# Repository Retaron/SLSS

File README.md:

# SLSS
Code for hobby project of mushroom manager

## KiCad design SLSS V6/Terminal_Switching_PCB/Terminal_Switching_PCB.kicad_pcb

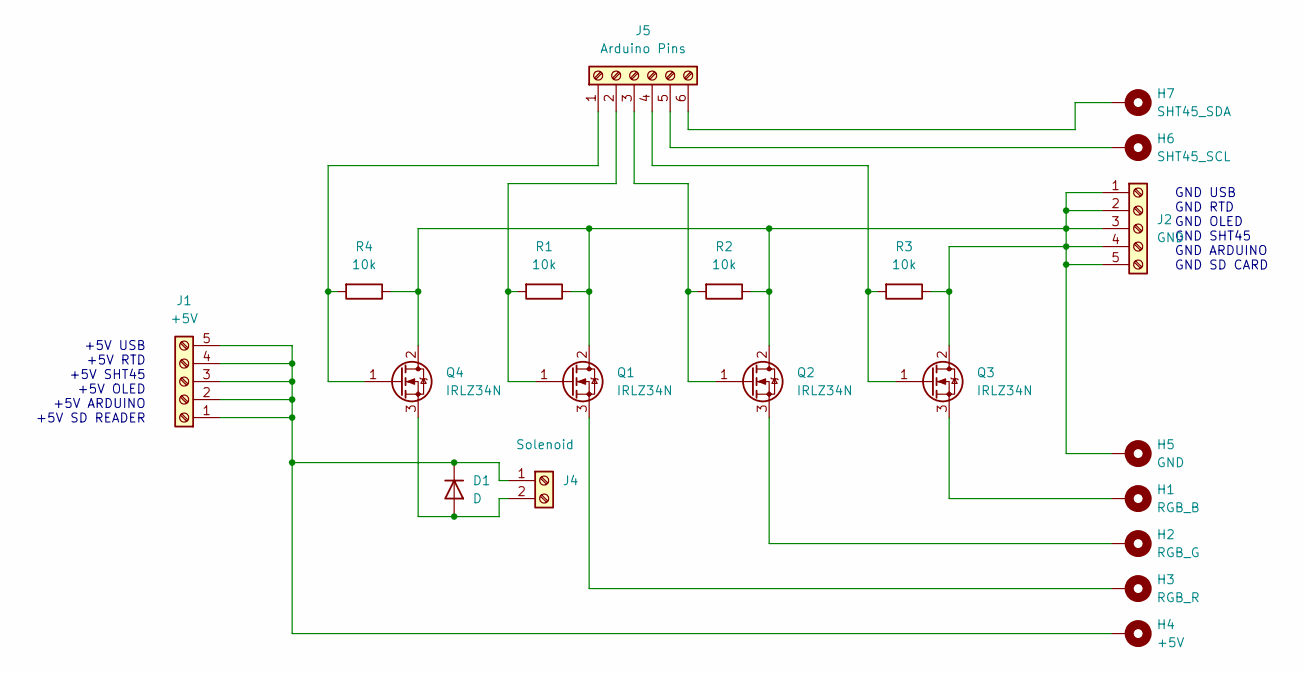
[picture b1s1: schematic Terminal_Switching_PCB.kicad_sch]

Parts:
D1: D; D_A-405_P10.16mm_Horizontal
H1: RGB_B; MountingHole_3.2mm_M3_Pad_Via
H2: RGB_G; MountingHole_3.2mm_M3_Pad_Via
H3: RGB_R; MountingHole_3.2mm_M3_Pad_Via
H4: +5V; MountingHole_3.2mm_M3_Pad_Via
H5: GND; MountingHole_3.2mm_M3_Pad_Via
H6: SHT45_SCL; MountingHole_3.2mm_M3_Pad_Via
H7: SHT45_SDA; MountingHole_3.2mm_M3_Pad_Via
J1: +5V; TerminalBlock_Phoenix_MPT-0,5-5-2.54_1x05_P2.54mm_Horizontal
J2: GND; TerminalBlock_Phoenix_MPT-0,5-5-2.54_1x05_P2.54mm_Horizontal
J4: Solenoid; JST_XH_B2B-XH-A_1x02_P2.50mm_Vertical
J5: Arduino Pins; TerminalBlock_Phoenix_MPT-0,5-6-2.54_1x06_P2.54mm_Horizontal
Q1, Q2, Q3, Q4: IRLZ34N; TO-220-3_Vertical
R1, R2, R3, R4: 10k; R_Axial_DIN0207_L6.3mm_D2.5mm_P10.16mm_Horizontal

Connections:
unnamed: D1.2 (A), J4.2, Q4.3 (S)
unnamed: D1.1 (K), H4.1 (1_1), J1.1, J1.2, J1.3, J1.4, J1.5, J4.1
unnamed: H5.1 (1_1), J2.1, J2.2, J2.3, J2.4, J2.5, Q1.2 (D), Q2.2 (D), Q3.2 (D), Q4.2 (D), R1.1, R2.1, R3.1, R4.1
unnamed: J5.1, Q4.1 (G), R4.2
unnamed: J5.2, Q1.1 (G), R1.2
unnamed: J5.3, Q2.1 (G), R2.2
unnamed: J5.4, Q3.1 (G), R3.2
unnamed: H6.1 (1_1), J5.5
unnamed: H7.1 (1_1), J5.6
unnamed: H3.1 (1_1), Q1.3 (S)
unnamed: H2.1 (1_1), Q2.3 (S)
unnamed: H1.1 (1_1), Q3.3 (S)

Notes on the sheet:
+5V USB +5V RTD +5V SHT45 +5V OLED +5V ARDUINO +5V SD READER
GND USB GND RTD GND OLED GND SHT45 GND ARDUINO GND SD CARD

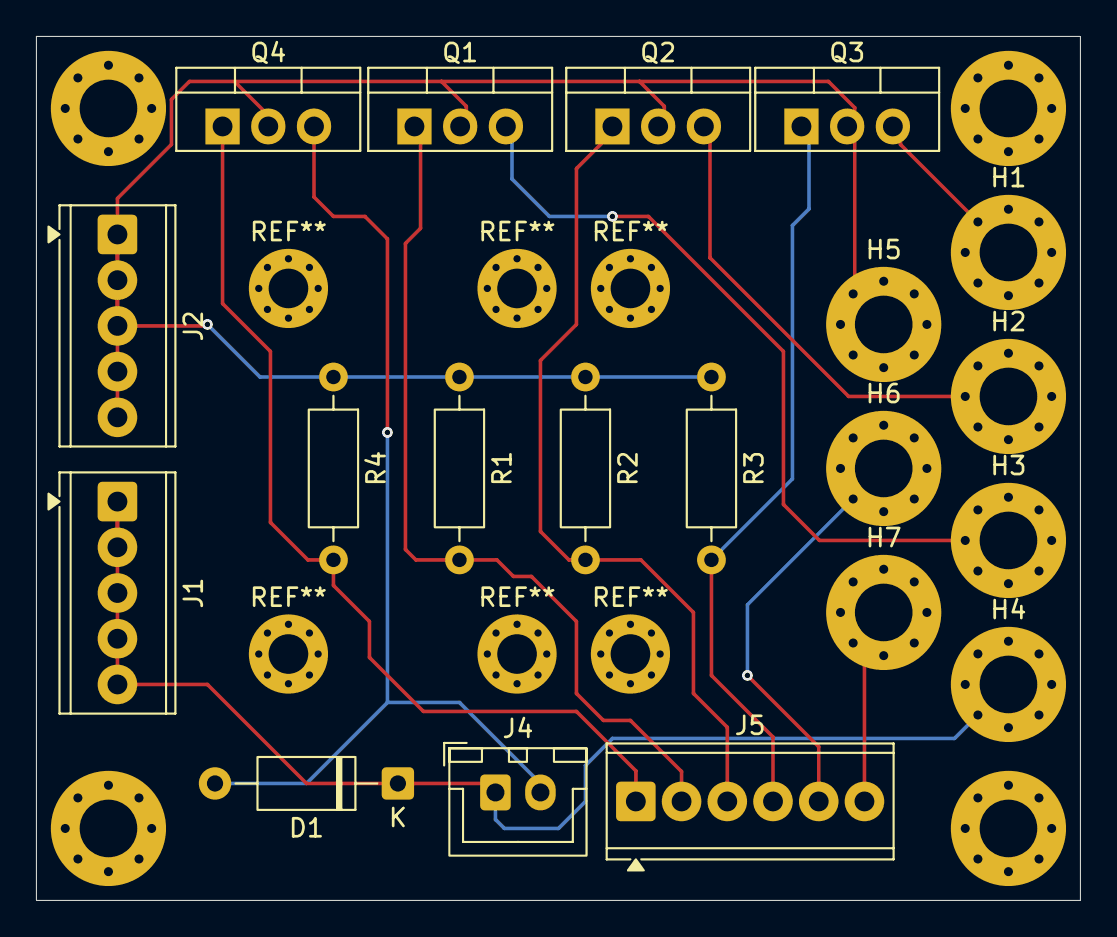
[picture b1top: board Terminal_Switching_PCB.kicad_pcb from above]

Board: 2 copper layers, 58.0 x 48.0 mm, 20 parts (0 on the bottom side), 12 nets.

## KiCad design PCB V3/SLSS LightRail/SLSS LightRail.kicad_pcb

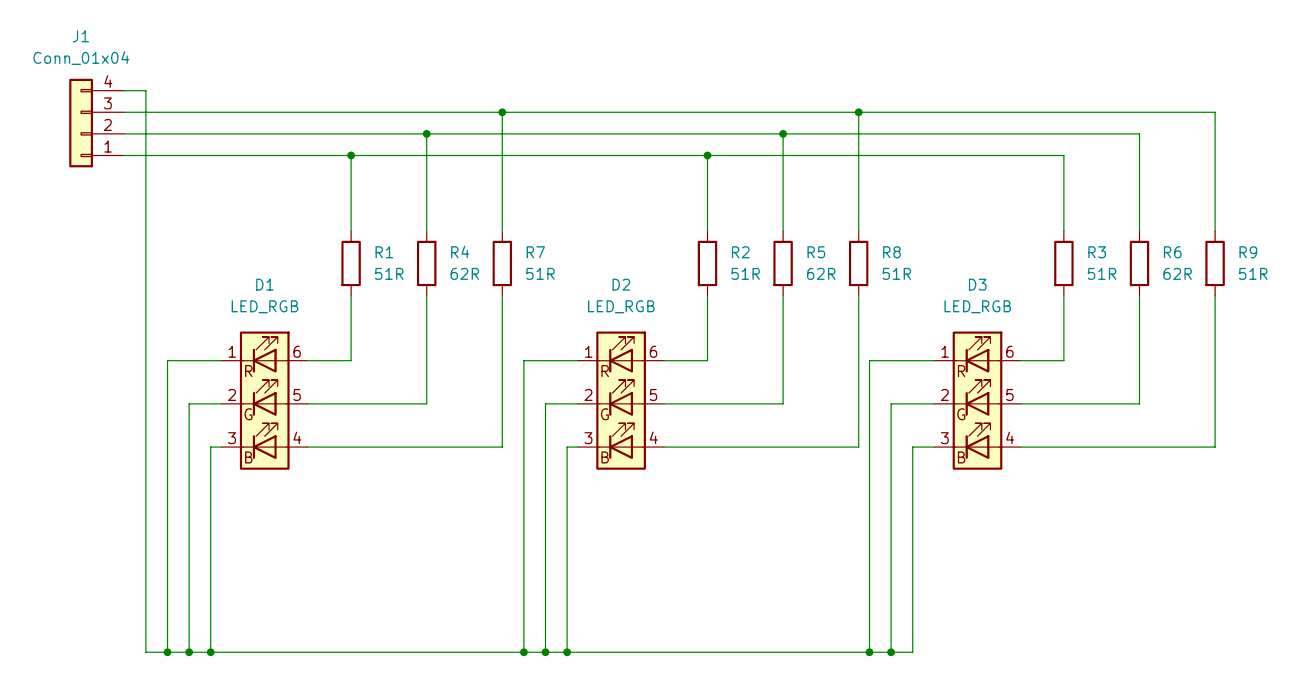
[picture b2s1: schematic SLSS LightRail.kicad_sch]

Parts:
D1, D2, D3: LED_RGB; LED_RGB_5050-6
J1: Conn_01x04; JST_GH_SM04B-GHS-TB_1x04-1MP_P1.25mm_Horizontal
R1, R2, R3, R7, R8, R9: 51R; R_1206_3216Metric
R4, R5, R6: 62R; R_1206_3216Metric

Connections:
unnamed: D1.4 (BA), R7.2
unnamed: D1.1 (RK), D1.2 (GK), D1.3 (BK), D2.1 (RK), D2.2 (GK), D2.3 (BK), D3.1 (RK), D3.2 (GK), D3.3 (BK), J1.4
unnamed: D1.5 (GA), R4.1
unnamed: D1.6 (RA), R1.2
unnamed: D2.4 (BA), R8.2
unnamed: D2.5 (GA), R5.2
unnamed: D2.6 (RA), R2.2
unnamed: D3.4 (BA), R9.2
unnamed: D3.5 (GA), R6.2
unnamed: D3.6 (RA), R3.2
unnamed: J1.1, R1.1, R2.1, R3.1
unnamed: J1.2, R4.2, R5.1, R6.1
unnamed: J1.3, R7.1, R8.1, R9.1

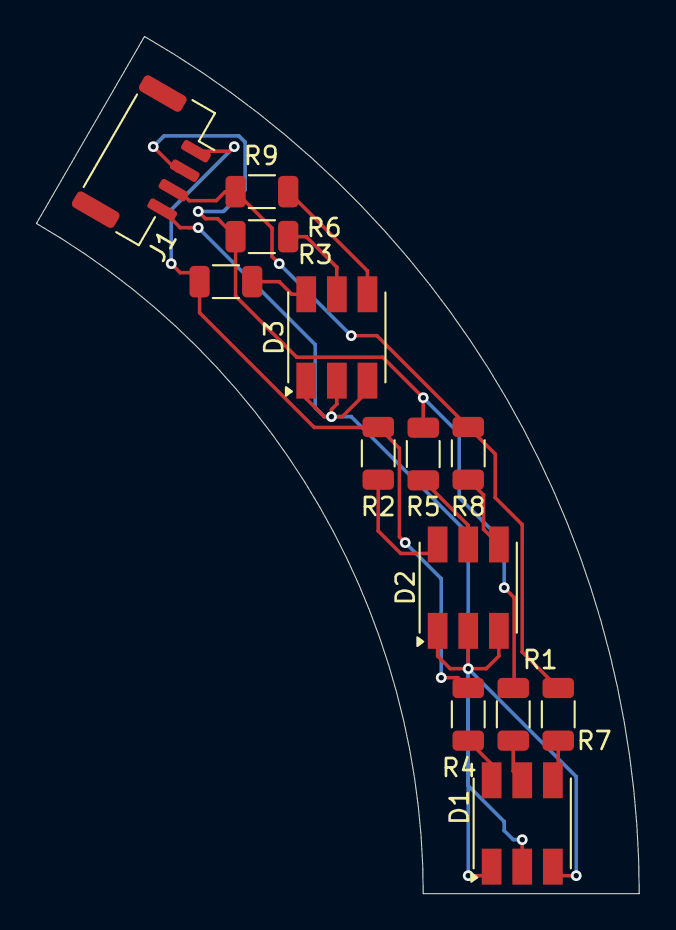
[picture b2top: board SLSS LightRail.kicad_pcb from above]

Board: 2 copper layers, 33.5 x 47.6 mm, 13 parts (0 on the bottom side), 13 nets.

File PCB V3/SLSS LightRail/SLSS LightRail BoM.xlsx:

Reference | Qty | Value | DNP | Exclude from BOM | Exclude from Board | Footprint | Datasheet | Manufacturer part number | Supplier part number | Supplier | Manufacturer
D1,D2,D3 | 3 | LED_RGB |  |  |  | LED_SMD:LED_RGB_5050-6 | KAAF-5050RGBS-13 LED Data Sheet | KAAF-5050RGBS-13 | 872-1724 | RS components | Kingbright
J1 | 1 | Conn_01x04 |  |  |  | Connector_JST:JST_XA_S04B-XASK-1_1x04_P2.50mm_Horizontal | Datasheet | S04B-XASK-1 (LF)(SN) | 602-8228 | RS components | JST
R1,R2,R3,R7,R8,R9 | 6 | 51R |  |  |  | Resistor_SMD:R_1206_3216Metric | Document - SR2512MK-071R3L | SR1206JR-0751RL | 197-8432 | RS components | Yageo
R4,R5,R6 | 3 | 62R |  |  |  | Resistor_SMD:R_1206_3216Metric | Datasheet - RC |  | 198-8437 | RS components | Yageo

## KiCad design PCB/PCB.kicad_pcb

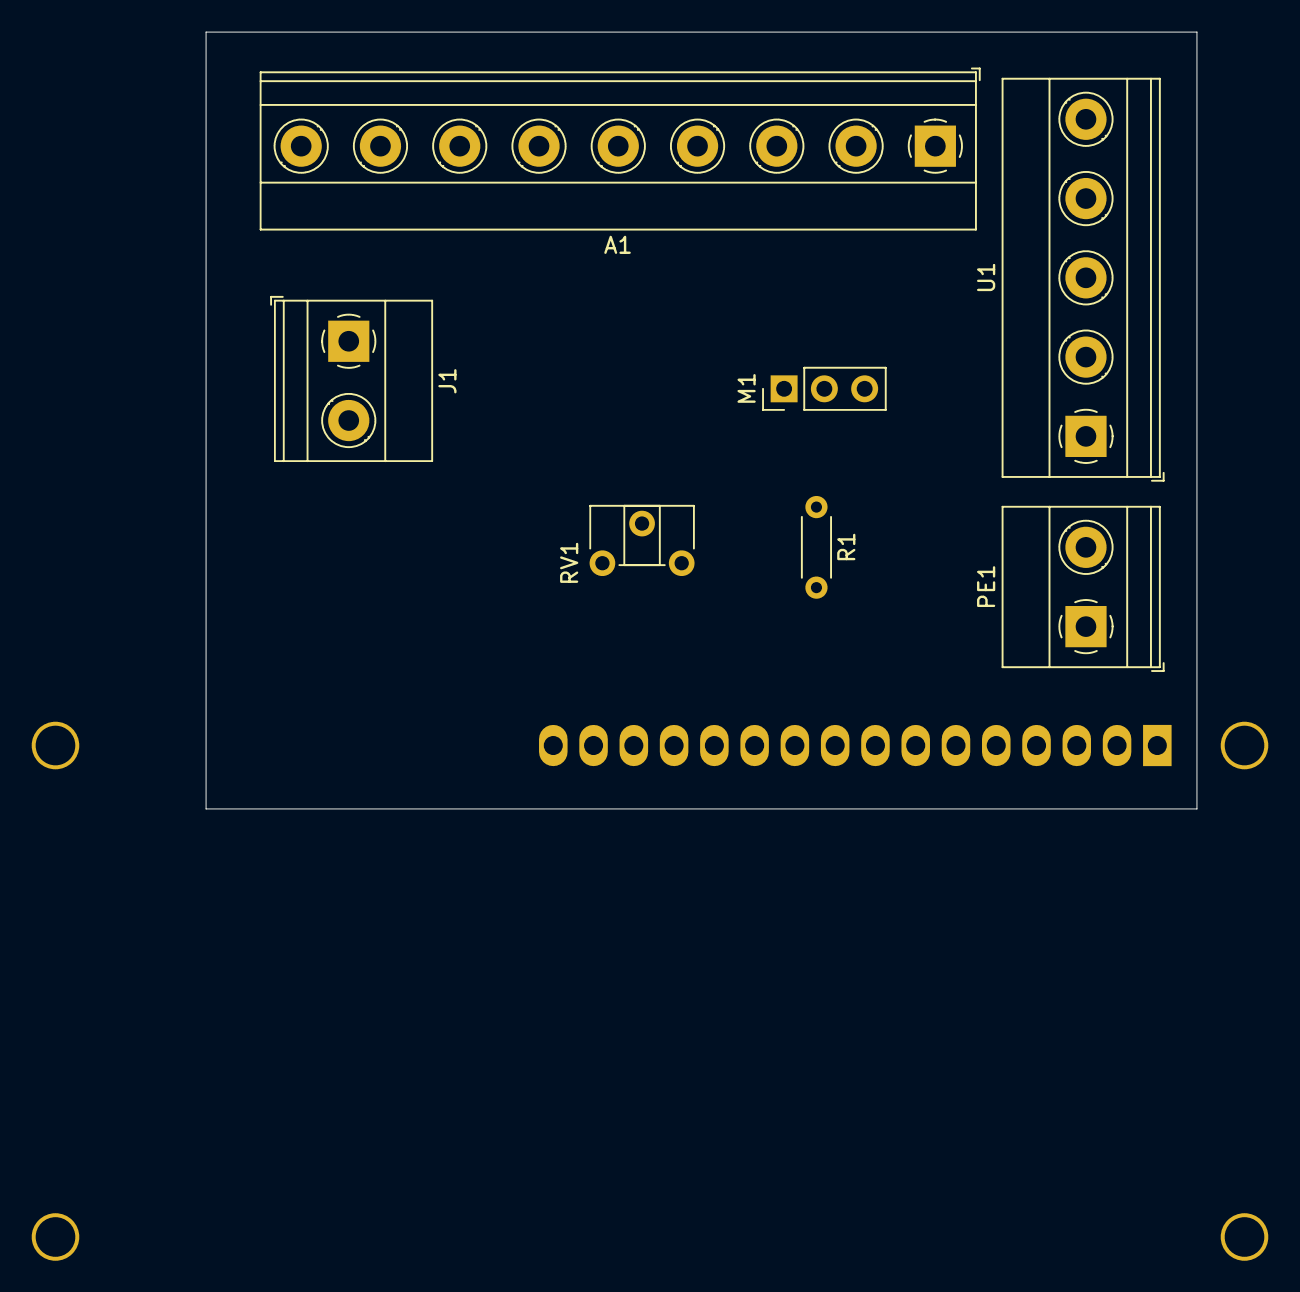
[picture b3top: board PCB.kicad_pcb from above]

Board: 2 copper layers, 62.5 x 49.0 mm, 8 parts (1 on the bottom side), 7 nets, no tracks yet.

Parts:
A1: Arduino_UNO_R3; TerminalBlock_Phoenix_MKDS-1,5-9_1x09_P5.00mm_Horizontal
DS1: WC1602A
J1: Barrel_Jack; TerminalBlock_Phoenix_MKDS-1,5-2_1x02_P5.00mm_Horizontal
M1: Motor_Servo; PinHeader_1x03_P2.54mm_Vertical
PE1: PeltierElement; TerminalBlock_Phoenix_MKDS-1,5-2_1x02_P5.00mm_Horizontal
R1: 220; R_Axial_DIN0204_L3.6mm_D1.6mm_P5.08mm_Horizontal
RV1: R_Potentiometer; Potentiometer_ACP_CA6-H2,5_Horizontal
U1: L298N; TerminalBlock_Phoenix_MKDS-1,5-5_1x05_P5.00mm_Horizontal

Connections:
unnamed: A1.5 (+5V), DS1.2 (VDD), R1.2, RV1.3
unnamed: DS1.15 (LED(+)), R1.1
unnamed: A1.7 (GND), DS1.1 (VSS), DS1.5 (R/W), DS1.16 (LED(-)), J1.2, RV1.1
unnamed: DS1.3 (VO), RV1.2
unnamed: PE1.1, U1.2 (OUT1)
unnamed: PE1.2, U1.3 (OUT2)
unnamed: J1.1, U1.4 (Vs)

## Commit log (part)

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2025-09-22 Created SLSS.ino
    Uploaded previously worked on SLSS.ino as a template and added function relating to reading from the current sensor
2025-09-22 minor changes
2025-09-23 Updated pins
    moved LCD pins to digital since they dont need PWM
2025-09-23 Rotary encoder & LCD Pages
    reorganised pins again due to rotary encoder only working on pins 2 & 3. added pages to LCD with rotary encoder.
    TODO: added click to modify values and possibly fix encoder direction accuraccy
2025-09-24 Fixed rotary encoder Inaccuracy
    fixed inaccuracy by stealing some strange serial code from somewhere else
2025-09-24 Better format + fixes
    adding a small delay fixes the occasional miss by the rotary encoder. Reformatted code for page interaction.
2025-09-24 began RGB edit
2025-09-25 Prototype RBG edit
    Added select for RGB values
2025-09-25 more rgb updates
2025-10-22 RGB edit implemented
    Fully implemented RGB page, including displaying the values and editing them using the rotary encoder
2025-10-22 Added RGB led pinout
    Added function and set the pins for the RGB LED
2025-10-23 broke it lol
2025-10-27 fixed page issue
    for whatever reason, when defining variables inside a function, the page wont change
2025-10-27 added switch
2025-10-28 krap
2025-10-29 DHT testing
    simple DHT11 sensor test, pretty sure the one I am using is broken
2025-10-29 Fixed DHT11
    fixed DHT11 by using a different library, the library recommends a polling rate of 1Hz however it seems to update instantly on the LCD when using the normal loops delay of 50ms
2025-10-30 Moved repo
2025-11-03 Update entire repo
2025-11-04 3D printng
2025-11-04 added external models
2025-11-06 3D prints
2025-11-10 Printing PSU box fast
    printing PSU box with fast parameters (0.6n 40mm layer height)
2025-11-15 Step files for collaboration
2025-11-18 external file
2025-11-18 V3
    YEsss James all is good
2025-11-18 Updated BOM
2025-11-19 new BoM for v3
2025-11-20 Did some more work
2025-11-21 Added bottle chassis prototype
2025-11-21 Yeess Some more work
2025-11-21 added part to bom
2025-11-21 iygv
2025-11-21 Started PCB
2025-11-22 testing github
2025-11-22 Started the 4 Verson
2025-11-23 Some Even More Work
2025-11-23 ouvy
2025-11-23 Updated KiCad Schematic
    Included arduino nano trace and USB-C connector
2025-11-24 Yeess
2025-11-24 yesss
2025-11-24 Added hatching to cover
2025-11-24 Added LCD and file management
2025-11-24 More Work
2025-11-25 Yresss
2025-11-25 Added filter patch hole
2025-11-25 spine
2025-11-25 YESA
2025-11-25 Yrwesa
2025-11-26 yeeesss
2025-11-26 Printed knob
2025-11-26 Minor changes
    renamed assembly, created air tunnel assembly
2025-11-27 Air tunnel rework
2025-11-27 PCB Backup
2025-11-27 Screen documentation
2025-11-27 Fan tunnel design
2025-11-27 Air Tunnel modifications
2025-11-28 V5 BOTTLE AND REQUIREMENTS
2025-11-29 TYCGHV
2025-11-29 Bottle servo push test
2025-11-30 Research of UV light
2025-11-30 LED mount
2025-12-01 Added SMD LED to BoM
2025-12-01 printing test rigs
2025-12-01 LED rail
2025-12-02 Began LED PCB
2025-12-02 Minor alterations to LED PCB
2025-12-02 horn gears
2025-12-03 light rail PCB
2025-12-03 Finished Lightrail PCB
2025-12-03 PCB size fix
2025-12-03 Mirror PCB
2025-12-03 Began bottle push mechanism
2025-12-04 Rack and pinion for servo
2025-12-04 3D Print gear
2025-12-06 drawer
2025-12-07 bottledrw
2025-12-07 shgfrga
2025-12-08 Rail partition
2025-12-10 bottle rail edit
2025-12-10 external latch model
2025-12-12 nothing
2025-12-22 drawer lokcing mechanism
2025-12-24 Lock mechanism
2025-12-27 printer files
2025-12-30 servo interface files
2026-01-02 servo interface
2026-01-03 Bottle Servo gear
2026-01-04 Gear draw
2026-01-05 print files
2026-01-05 test rig for draw
2026-01-18 air tunnel rework
    reworked air tunnel so it can be sealed
2026-01-19 3D Print files
2026-01-20 heat sink fit
2026-03-02 Gear test rework
2026-03-06 3d print file
2026-03-10 Ordered PCB
2026-03-12 rework clamp design
2026-03-12 bleh
2026-03-12 backup ig
2026-06-06 Created assembly
2026-06-07 New assembly with lightrail
    created the assembly with the lightrail along with its fixtures. updated the bom with the fixtures
2026-06-07 nchange
2026-06-07 yess
2026-06-08 Solenoid and clamp
2026-06-09 slight alt
2026-06-11 Small changes
2026-06-19 Solidified the base model so it can be better exapnded upon
2026-06-22 jst 3d print files gng
